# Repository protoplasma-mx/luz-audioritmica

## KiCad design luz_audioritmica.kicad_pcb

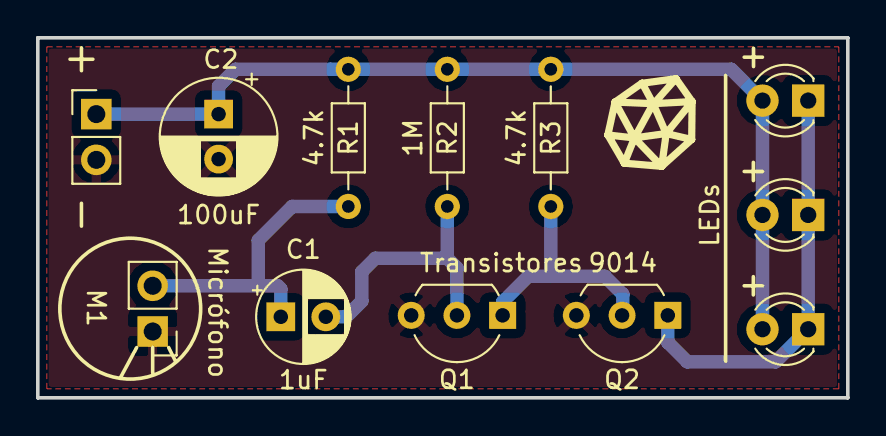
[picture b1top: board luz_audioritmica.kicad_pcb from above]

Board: 2 copper layers, 45.0 x 20.0 mm, 8 parts (0 on the bottom side), 5 nets.

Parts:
C1: 1uF; CP_Radial_D5.0mm_P2.50mm
C2: 100uF; CP_Radial_D6.3mm_P2.50mm
M1: Micrófono; PinHeader_1x02_P2.54mm_Vertical
Q1: Transistores; TO-92L_Inline_Wide
Q2: 9014; TO-92L_Inline_Wide
R1, R3: 4.7k; R_Axial_DIN0204_L3.6mm_D1.6mm_P7.62mm_Horizontal
R2: 1M; R_Axial_DIN0204_L3.6mm_D1.6mm_P7.62mm_Horizontal

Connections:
GNDREF: C2.2, M1.1, Q1.3, Q2.3
unnamed: C1.1, M1.2, R1.2
unnamed: C1.2, Q1.2, R2.2
unnamed: Q1.1, Q2.2, R3.2
VCC: C2.1, R1.1, R2.1, R3.1

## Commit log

2019-07-16 Commit original
